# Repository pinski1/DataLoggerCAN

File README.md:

#Data Logger CAN
A data logger.

Connect to a CAN network of VESCs and log data.
Data is logged to a local SD card and also transmitted via XBee.

##Hardware

*SD Card
*Teensy 3.2
*XBee

##Licence
w/e

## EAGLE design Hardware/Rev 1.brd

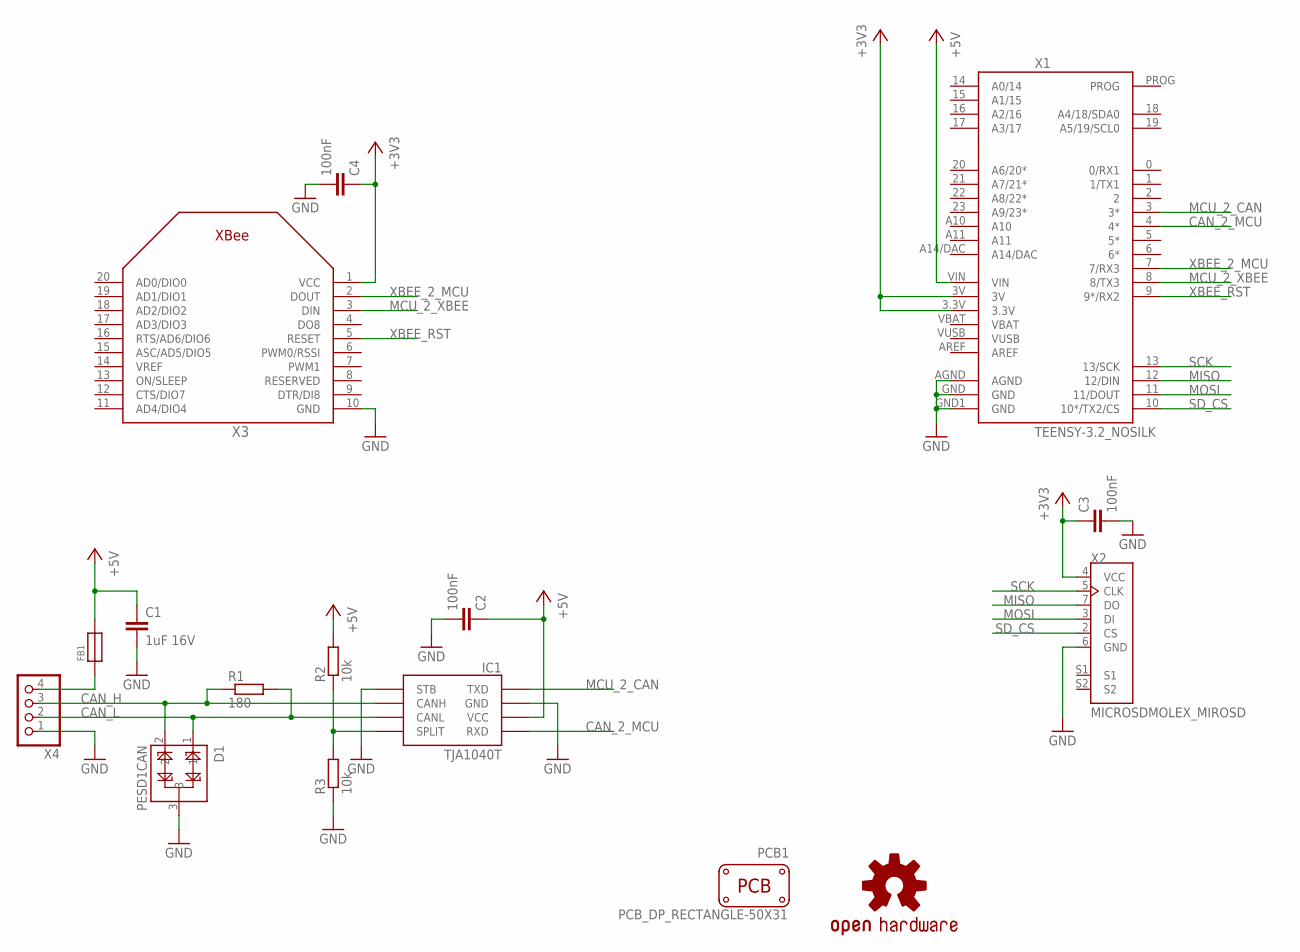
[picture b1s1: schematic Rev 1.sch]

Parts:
C1: 1uF 16V; C1206
C2, C3, C4: 100nF; C0603
D1: PESD1CAN; SOT23-3
FB1: FERRITE; 0603
IC1: TJA1040T; SO08
LOGO1: OSHW-LOGOM; OSHW-LOGO-M
PCB1: PCB_DP_RECTANGLE-50X31; DP5031_V1
R1: 180; R0603
R2, R3: 10k; R0603
X1: TEENSY-3.2_NOSILK; TEENSY-3.1_NOSILK
X2: MICROSDMOLEX_MIROSD; MOLEX_MICROSD
X3: XBEE
X4: JST_4PIN; JSTPH4

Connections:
+3V3: C3.1, C4.1, X1.3.3V, X1.3V, X2.4 (VCC), X3.1 (VCC)
+5V: C1.1, C2.1, FB1.2, IC1.3 (VCC), R2.2, X1.VIN
+5V_RAW: FB1.1, X4.4
CAN_2_MCU: IC1.4 (RXD), X1.4 (4*)
CAN_H: D1.2, IC1.7 (CANH), R1.1, X4.3
CAN_L: D1.1, IC1.6 (CANL), R1.2, X4.2
GND: C1.2, C2.2, C3.2, C4.2, D1.3, IC1.2 (GND), IC1.8 (STB), R3.1, X1.AGND, X1.GND, X1.GND1 (GND), X2.6 (GND), X3.10 (GND), X4.1
MCU_2_CAN: IC1.1 (TXD), X1.3 (3*)
MCU_2_XBEE: X1.8 (8/TX3), X3.3 (DIN)
MISO: X1.12 (12/DIN), X2.7 (DO)
MOSI: X1.11 (11/DOUT), X2.3 (DI)
unnamed: IC1.5 (SPLIT), R2.1, R3.2
SCK: X1.13 (13/SCK), X2.5 (CLK)
SD_CS: X1.10 (10*/TX2/CS), X2.2 (CS)
XBEE_2_MCU: X1.7 (7/RX3), X3.2 (DOUT)
XBEE_RST: X1.9 (9*/RX2), X3.5 (RESET)

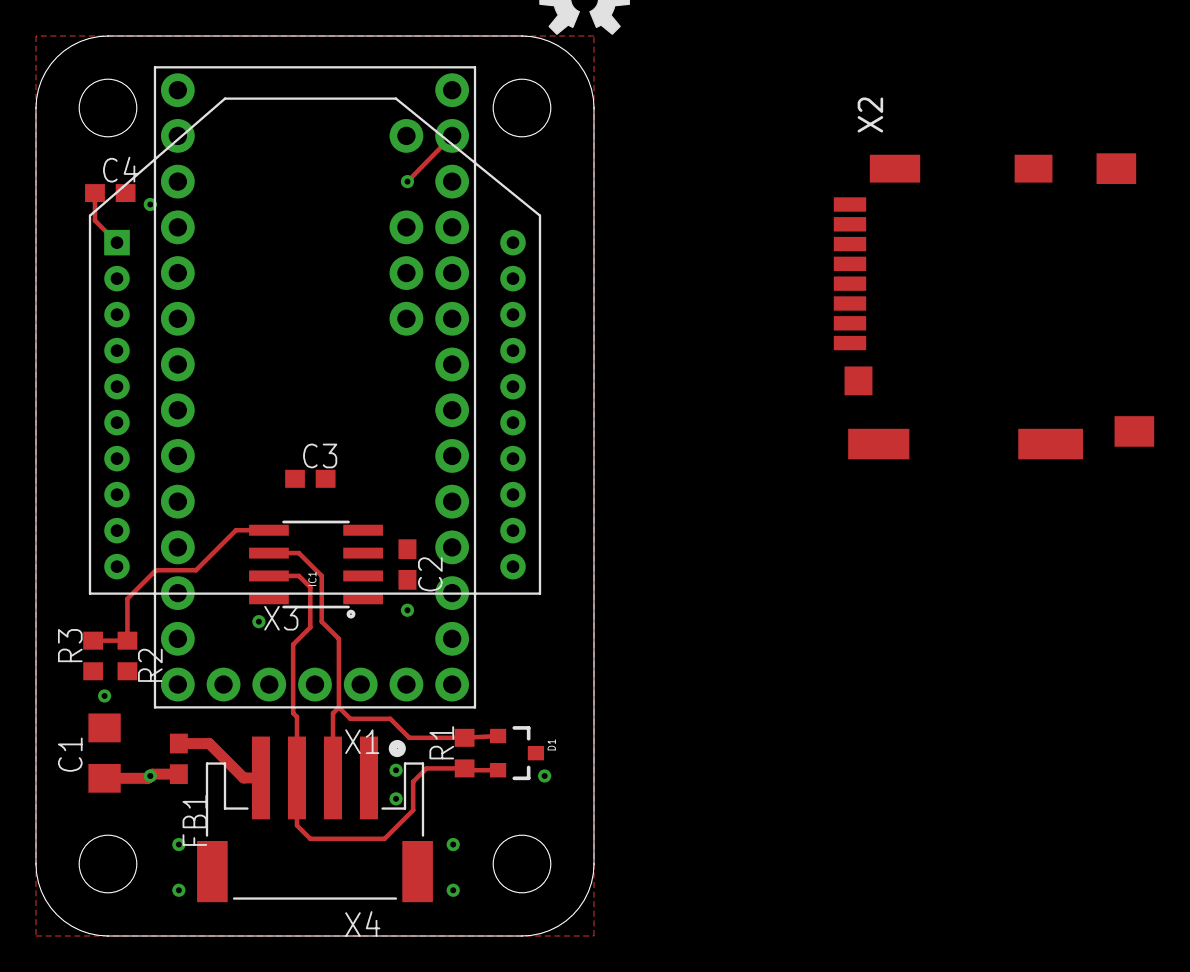
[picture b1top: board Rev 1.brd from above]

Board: 2 copper layers, 31.0 x 50.0 mm, 16 parts (0 on the bottom side), 16 nets.

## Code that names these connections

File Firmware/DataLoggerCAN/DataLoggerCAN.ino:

/** Datalogger for CAN messages
   @detail Logs CAN messages from a network of connected VESC speed controllers. These messages will be saved locally to SD card (with timestamps) as well as transmitted via XBee to a remote terminal
   
   Requires:
     SD Card
     XBee RF TRX
     Teensy 3.2
   
   Can't seem to find any concrete information on VESC CANBUS messages. I'm assuming each VESC (once programmed with a unique ID) will transmit status messages including:
     battery voltage, current, board temperature, motor temperature, motor RPMs, throttle
   The plan will be to log this to the SD card with timestamps (Teensy 3.2 includes a real time clock)
   In addition certain information (undecided as to which) will be forwarded via XBee for real time feedback

   @status just place holder code for now.

   @author @pinski1_
   @date 06/09/2016

*/
#include <XBee.h>
#include <FlexCAN.h>
#include <SPI.h>
#include <SdFat.h>

/** Settings */
#define USB_COM_SPEED 115200
#define XBEE_COM_SPEED 115200
#define CAN_COM_SPEED 500000
// file names
#define SECRET_KEY 0xFFFFFFFF // secret key to encrypt telemetry
#define DEBUG_EN (1) // enable debug messages via USB serial

/** Pin Map */
#define MCU_2_XBEE      8
#define XBEE_2_MCU      7
#define CAN_2_MCU       4
#define MCU_2_CAN       3
#define LED_ACT         13
#define LED_STA         6
#define USB_2_MCU       6
#define MCU_2_USB       6
#define MOSI            11
#define MISO            12
#define SCK             13
#define CS_SD           10
#define SW_SD           6

/** Globals */
FlexCAN CANbus(CAN_COM_SPEED);
SdFat sdCard;
SdFile dataFile;
char fileName[] = "LOGGER00.CSV";
XBee xbee = XBee();
static CAN_message_t msg, rxmsg;

/* Prototypes */
void logHeaders(void);


void setup(void) {

  /* GPIO init */
  pinMode(SW_SD, INPUT);
  pinMode(CS_SD, OUTPUT);
  pinMode(LED_STA, OUTPUT);
  pinMode(LED_ACT, OUTPUT);  
  digitalWrite(CS_SD, HIGH);
  digitalWrite(LED_STA, LOW);
  digitalWrite(LED_ACT, LOW);
  
  /* Coms init */
  Serial.begin(USB_COM_SPEED);
  Serial3.begin(XBEE_COM_SPEED);
  xbee.setSerial(Serial3);
  CANbus.begin();

  /* Storage init */
  // code to setup SD card or throw a wobbly if not found
  // don't want it to stop telemetry

  /*
      // start setting up log file
  Serial.println(F("Initializing SD card..."));
  if (!sdCard.begin(SD_CD))
  {
    Serial.println(F("SD card failed, or not present"));
    digitalWrite(LED_RED, HIGH);
    while (1);
  }
  Serial.println(F("SD card initialized."));

  for (uint8_t i = 0; i < 100; i++)
  {
    fileName[6] = i / 10 + '0';
    fileName[7] = i % 10 + '0';
    if (!=sdCard.exists(fileName))
    {
      // only open a new file if it doesn't exist
      logFile = sdCard.open(fileName, FILE_WRITE);
      break;  // leave the loop!
    }
  }

  if (!logFile)
  {
    Serial.print(F("Couldn't create log file on SD card."));
    digitalWrite(LED_RED, HIGH);
    while (1);
  }

   */


  
}

void loop(void) {

// read messages
 //CANbus.read(rxmsg);

 // save to SD card

 // transmit general status

 // delay to avoid overloading logs
}

void logHeaders(void) {

  // add headers to log file
  
  //logFile.print("VESC Log\r\nTime,Sequence,value1,value2,value3,value4,value5,etc\r\n");
  //logFile.close();

}

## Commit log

2016-09-06 :lollipop: Added .gitattributes & .gitignore files
2016-09-06 initial commit
    initial check in, has placeholder files.
2016-09-07 Further documentation and some code cleanup.
2016-09-07 Minor changes, adding some structure

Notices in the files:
parts and their libraries:
SparkFun-DigitalIC: Licensing: Creative Commons ShareAlike 4.0 International - https://creativecommons.org/licenses/by-sa/4.0
